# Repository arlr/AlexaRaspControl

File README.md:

# AlexaRaspControl
Utiliser Amazon Alexa pour intéragir avec des appareils connectés en bleutooth à une Raspberry PI

Installer : 

    sudo apt-get install python-pip python-dev ipython
    sudo apt-get install bluetooth libbluetooth-dev
    sudo pip install pybluez
    pip3 -> "sudo apt install python3-pip"
    Flask-Ask -> "sudo pip3 install flask-ask"

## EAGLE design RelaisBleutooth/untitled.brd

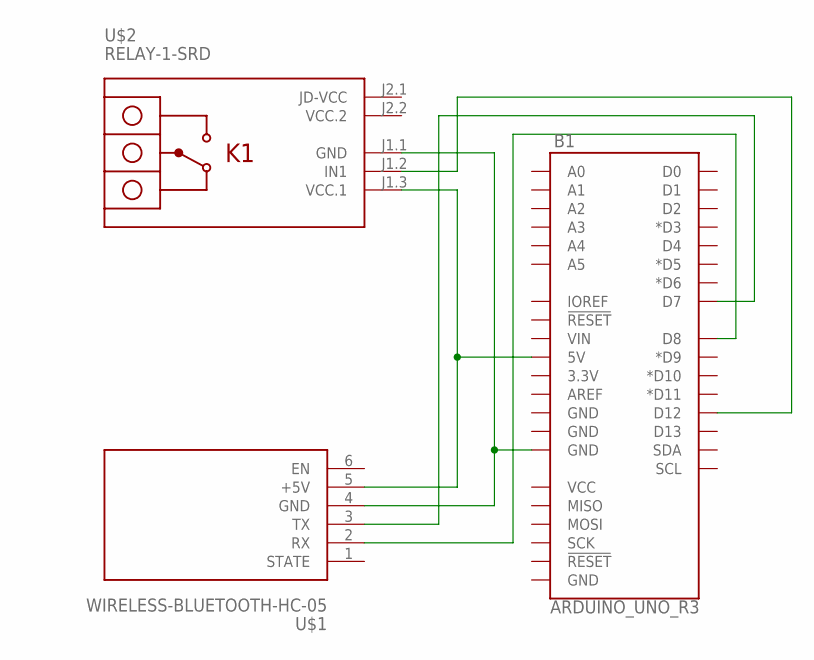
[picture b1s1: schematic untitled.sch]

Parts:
B1: ARDUINO_UNO_R3; ARDUINO_R3
U$1: WIRELESS-BLUETOOTH-HC-05
U$2: RELAY-1-SRD

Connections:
unnamed: B1.5V, U$1.5 (+5V), U$2.J1.3 (VCC.1)
unnamed: B1.D12, U$2.J1.2 (IN1)
unnamed: B1.GND@2 (GND), U$1.4 (GND), U$2.J1.1 (GND)
unnamed: B1.D7, U$1.3 (TX)
unnamed: B1.D8, U$1.2 (RX)
VCC.2: U$2.J2.2 (VCC.2)

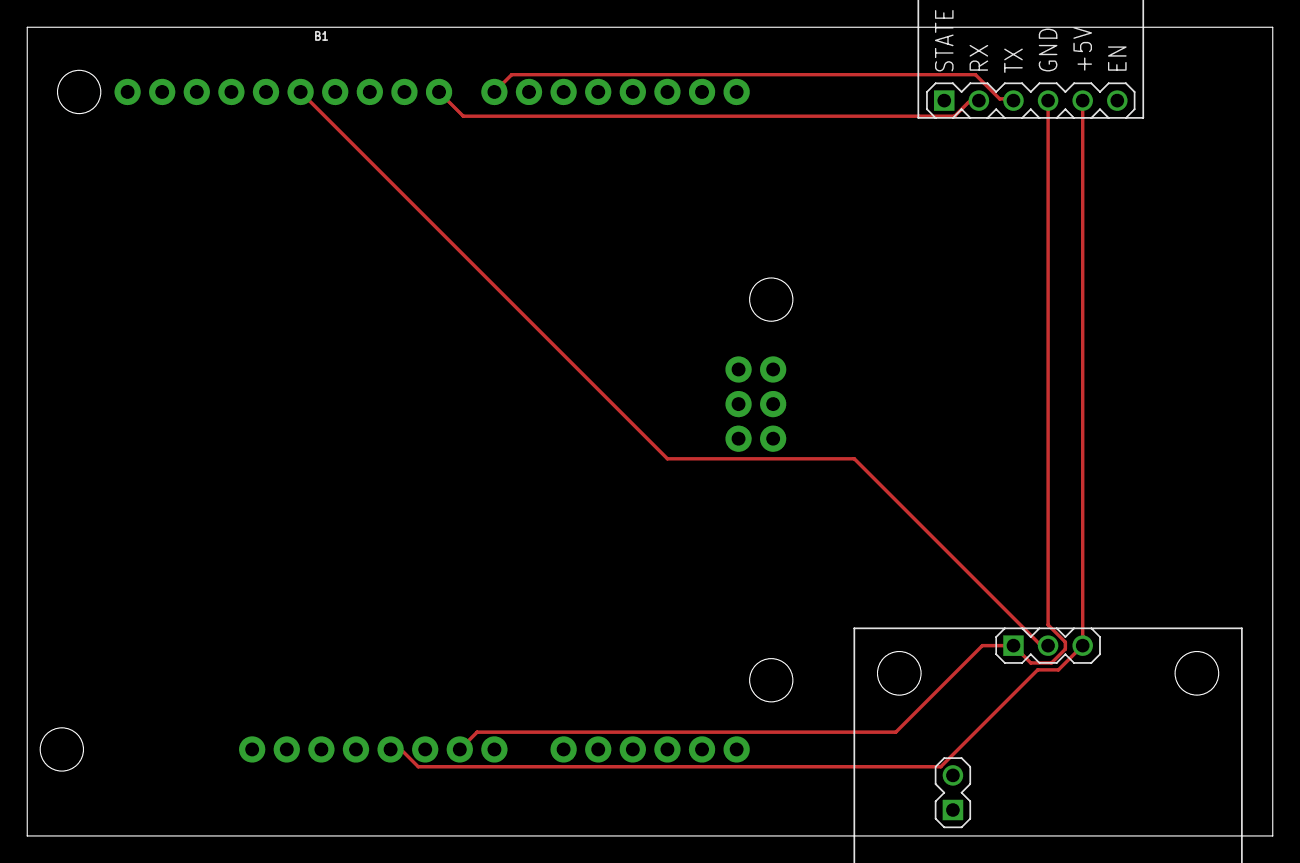
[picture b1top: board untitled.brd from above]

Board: 2 copper layers, 91.4 x 59.4 mm, 3 parts (0 on the bottom side), 5 nets.

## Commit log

2018-12-23 Schéma
2018-12-23 Ajout du main.py
2018-12-23 Mouvement de main.py dans le dossier raspberry
2018-12-23 Ajout de main.py et du dossier Raspi
2018-12-23 Ajout entête python
2018-12-23 Ajout Recherche bleutooth
2018-12-23 fautes
2018-12-24 Mise a jour des schema
2018-12-24 ajout du script alexa
2018-12-24 Creation script
2018-12-26 Ajout trucs
2018-12-26 DebutCreation code arduino
2018-12-26 PRemiere vertion du code Arduino
2018-12-26 ajout de commentaires
2018-12-27 mpoiuytrfvbnkl
2018-12-28 Creation d'un shea de fonctionnement et mise en place de script python pour la recherche d'appareil bluetooth
2018-12-28 passage a python3
2018-12-28 test de la fonction ListBL
2018-12-28 test liste
2018-12-28 test
2018-12-28 Test et premier essays sur alexa
2018-12-28 modif pip -> pip3
2018-12-29 tests
2018-12-29 prepare le premier test
2018-12-29 preparation premier test
2018-12-29 eddition des message
2018-12-30 arlr
2018-12-30 sdfgh
2018-12-30 dfghj
2018-12-30 qsdfghjk
2018-12-30 Ajout le fonction pour afficher les resultat du scann bluettoh
2018-12-30 je sais plus
2018-12-30 blalbla
2018-12-30 cotrrection
2018-12-30 appele des sous programmes
2018-12-30 Delete ScanBL.py
    Parceque ça marche pas
2018-12-30 ajout truc
2018-12-30 essais
2018-12-30 Mise en forme des ecriture de fichier
2018-12-30 corection
2018-12-30 test mise form string
2018-12-31 changement d'acces aux sous programmes
2018-12-31 idiot
2018-12-31 modification
2018-12-31 Update README.md
    changement du titre du readme

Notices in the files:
parts and their libraries:
SparkFun-Boards: Licensing: Creative Commons ShareAlike 4.0 International - https://creativecommons.org/licenses/by-sa/4.0
diy-modules: Released under the Creative Commons Attribution 4.0 International License: http://creativecommons.org/licenses/by/4.0
